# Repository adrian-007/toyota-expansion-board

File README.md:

# Toyota Expansion Board

This is a firmware source code for [Expansion Board](https://adrian-007.eu/2021/02/21/toyota-expansion-board-intro/) I made for my Toyota Corolla after replacing stock radio unit.

Firmware was written in C++14 for ATmega88 MCU and features:

* DS18B20 temperature reading
* SSD1306 OLED display driver
* Six buttons reading via ADC
* Communication with Pioneer radio unit via digital potentiometer MCP42100
* UART output (logging)

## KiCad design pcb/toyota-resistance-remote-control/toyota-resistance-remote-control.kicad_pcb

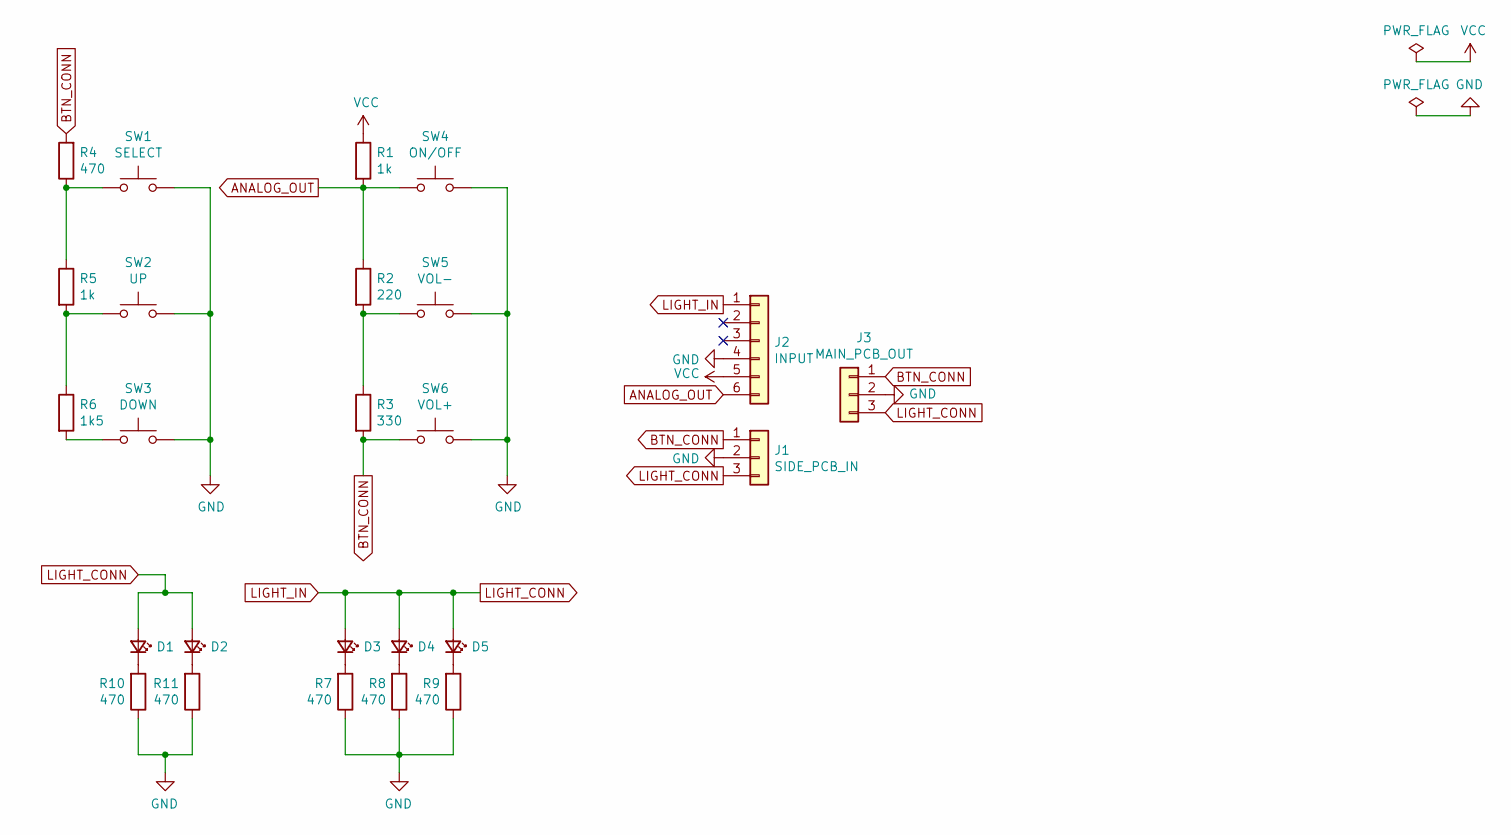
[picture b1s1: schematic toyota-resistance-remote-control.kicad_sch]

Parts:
D1, D2, D3, D4, D5: LED_Small; LED_D3.0mm
J1: SIDE_PCB_IN; PinHeader_1x03_P2.54mm_Vertical
J2: INPUT; PinHeader_1x06_P2.54mm_Vertical
J3: MAIN_PCB_OUT; PinHeader_1x03_P2.54mm_Vertical
R1, R5: 1k; R_1206_3216Metric_Pad1.42x1.75mm_HandSolder
R2: 220; R_1206_3216Metric_Pad1.42x1.75mm_HandSolder
R3: 330; R_1206_3216Metric_Pad1.42x1.75mm_HandSolder
R4, R7, R8, R9, R10, R11: 470; R_1206_3216Metric_Pad1.42x1.75mm_HandSolder
R6: 1k5; R_1206_3216Metric_Pad1.42x1.75mm_HandSolder
SW1: SELECT; SW_PUSH_6mm
SW2: UP; SW_PUSH_6mm
SW3: DOWN; SW_PUSH_6mm
SW4: ON/OFF; SW_PUSH_6mm
SW5: VOL-; SW_PUSH_6mm
SW6: VOL+; SW_PUSH_6mm

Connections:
ANALOG_OUT: J2.6, R1.2, R2.1, SW4.1
BTN_CONN: J1.1, J3.1, R3.2, R4.2, SW6.1
GND: J1.2, J2.4, J3.2, R7.1, R8.1, R9.1, R10.1, R11.1, SW1.2, SW2.2, SW3.2, SW4.2, SW5.2, SW6.2
LIGHT_CONN: D1.2 (A), D2.2 (A), D3.2 (A), D4.2 (A), D5.2 (A), J1.3, J2.1, J3.3
unnamed: D1.1 (K), R10.2
unnamed: D2.1 (K), R11.2
unnamed: D3.1 (K), R7.2
unnamed: D4.1 (K), R8.2
unnamed: D5.1 (K), R9.2
unnamed: R2.2, R3.1, SW5.1
unnamed: R4.1, R5.1, SW1.1
unnamed: R5.2, R6.1, SW2.1
unnamed: R6.2, SW3.1
VCC: J2.5, R1.1

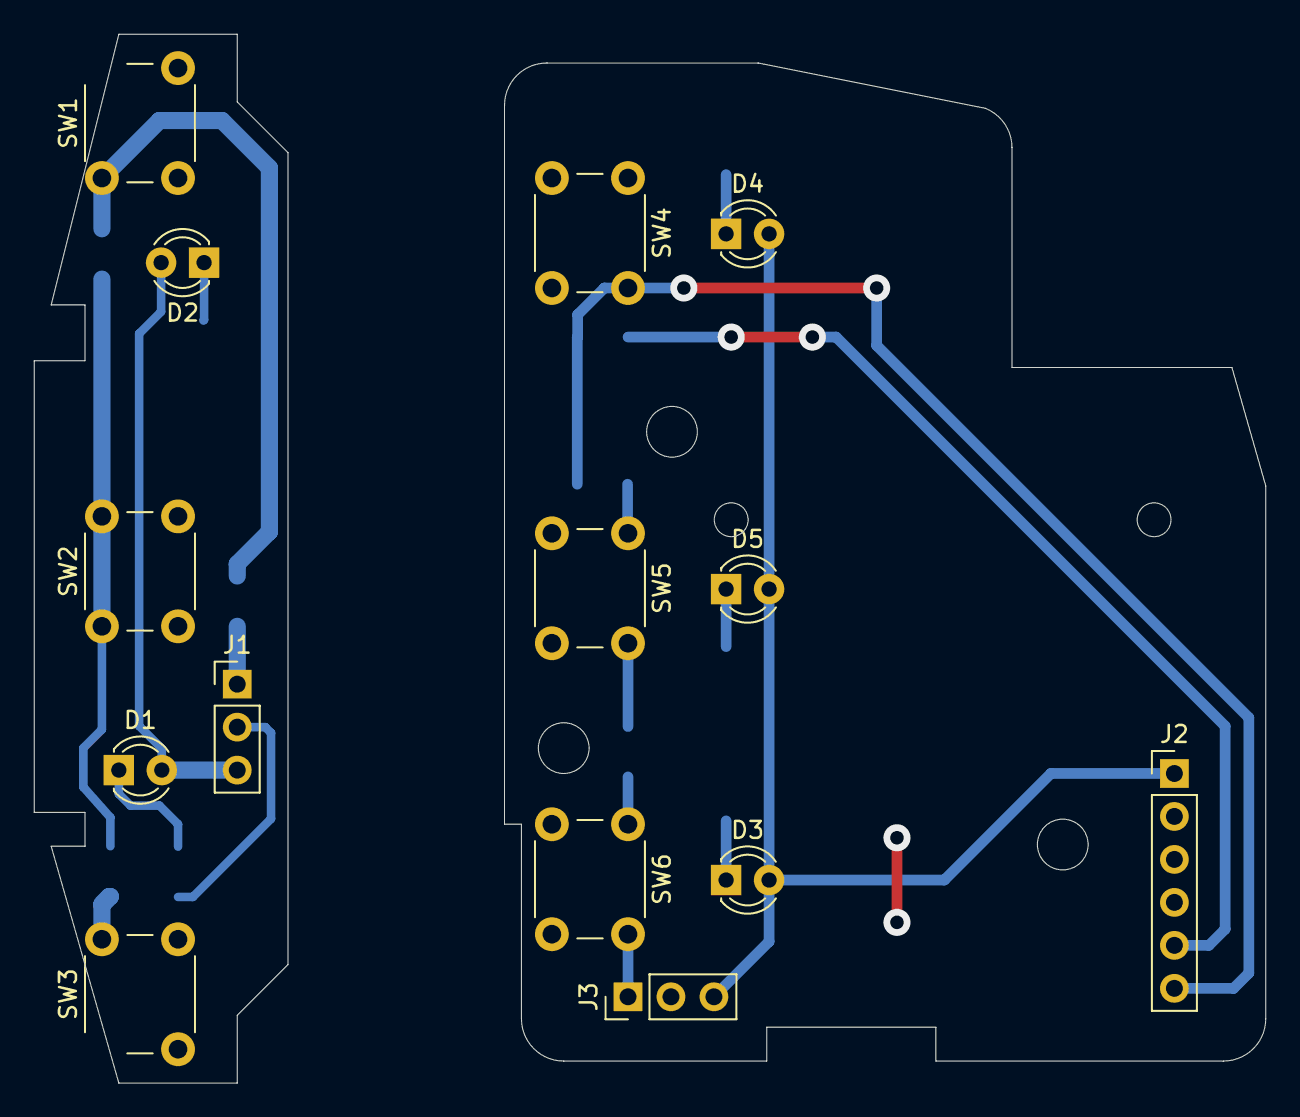
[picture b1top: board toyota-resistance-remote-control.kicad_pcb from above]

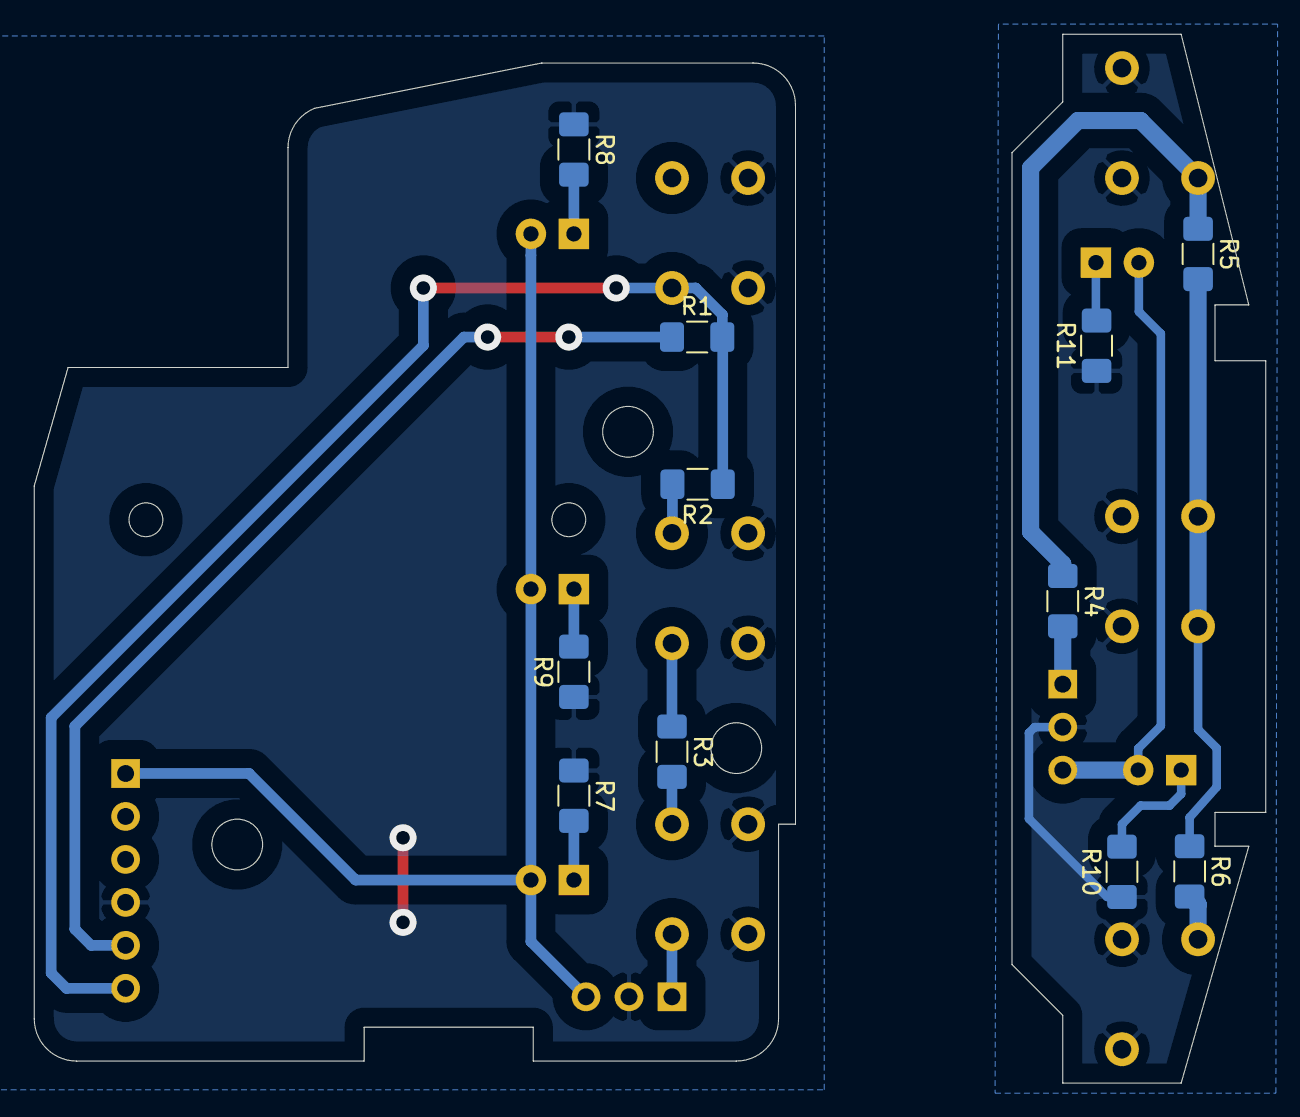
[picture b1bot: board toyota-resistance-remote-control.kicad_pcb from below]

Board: 2 copper layers, 72.8 x 62.0 mm, 25 parts (11 on the bottom side), 14 nets.

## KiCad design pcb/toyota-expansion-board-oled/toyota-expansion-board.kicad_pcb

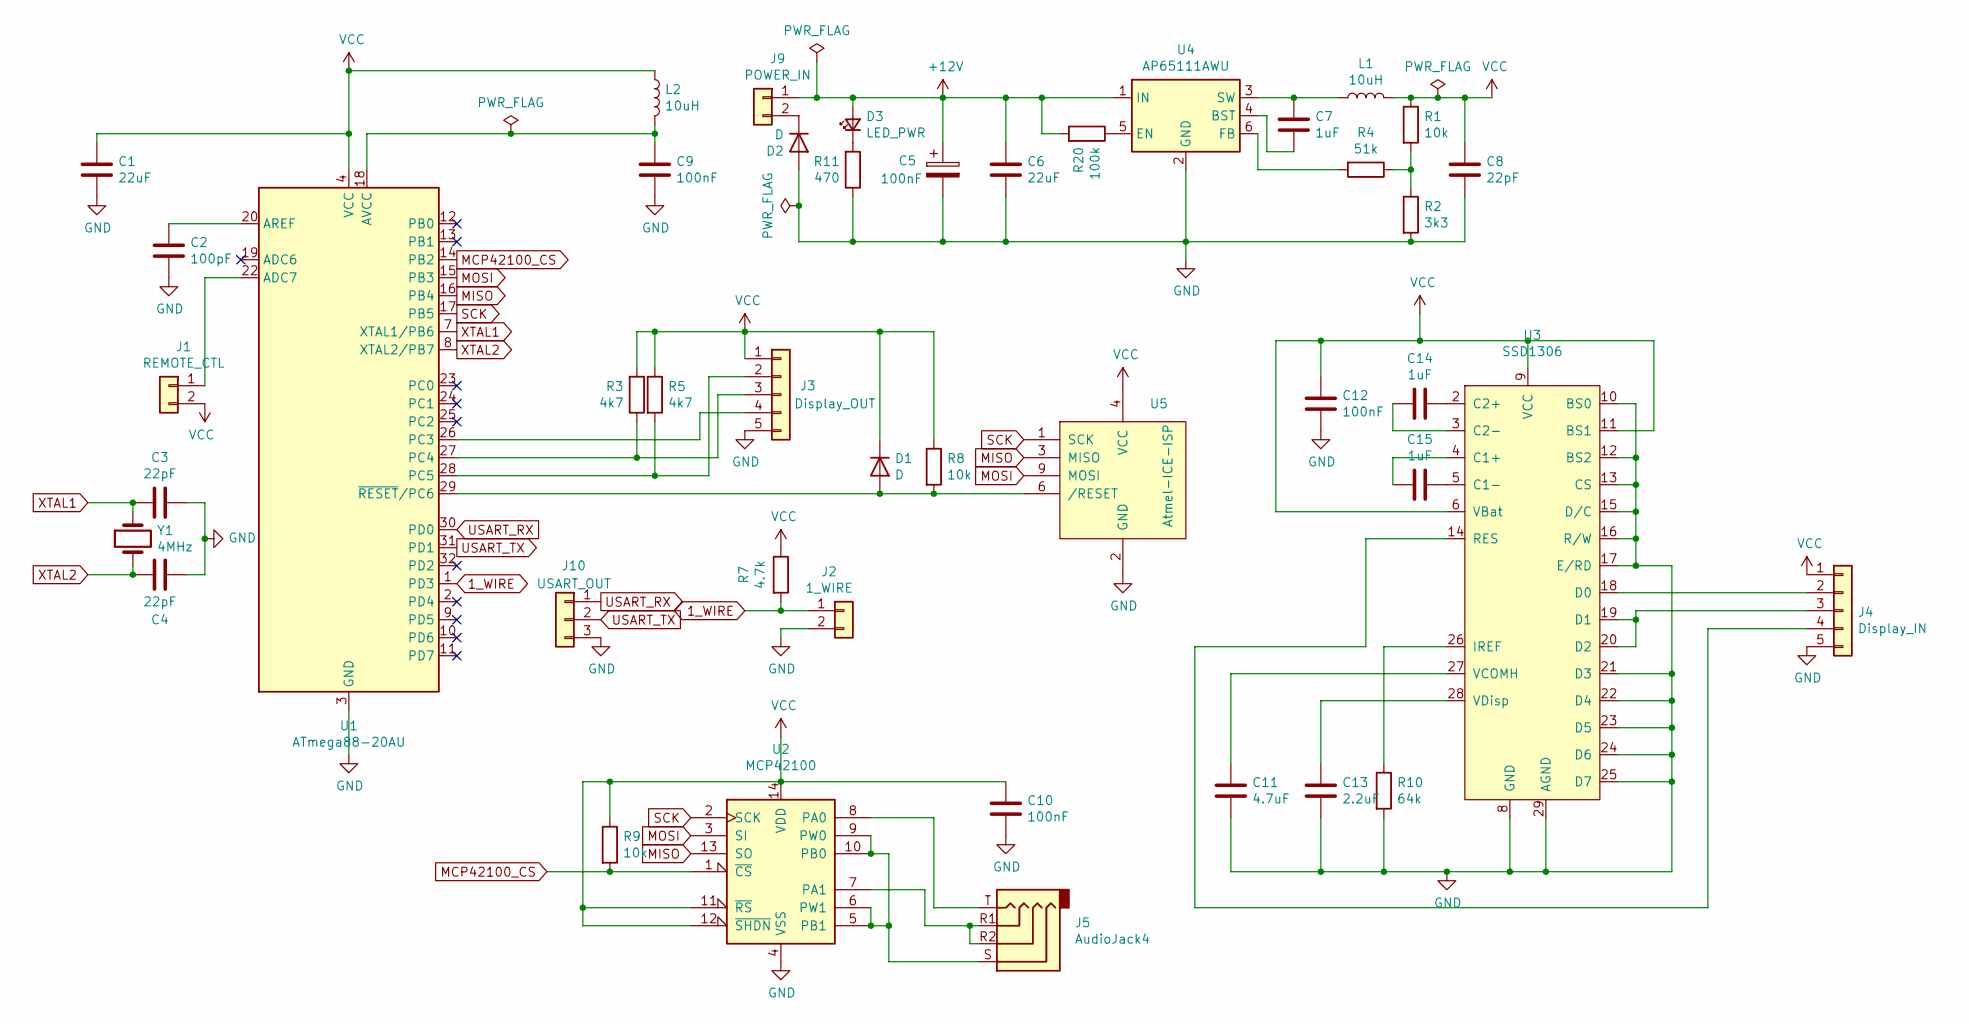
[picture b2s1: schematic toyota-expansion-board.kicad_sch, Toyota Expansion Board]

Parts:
C1, C6: 22uF; CP_Elec_6.3x5.4
C2: 100pF; C_1206_3216Metric_Pad1.33x1.80mm_HandSolder
C3, C4, C8: 22pF; C_1206_3216Metric_Pad1.33x1.80mm_HandSolder
C5, C9, C10, C12: 100nF; C_1206_3216Metric_Pad1.33x1.80mm_HandSolder
C7, C14, C15: 1uF; CP_Elec_4x5.4
C11: 4.7uF; CP_Elec_6.3x5.4
C13: 2.2uF; CP_Elec_6.3x5.4
D1, D2: D; D_DO-15_P5.08mm_Vertical_AnodeUp
D3: LED_PWR; LED_D3.0mm
J1: REMOTE_CTL; TerminalBlock_bornier-2_P5.08mm
J2: 1_WIRE; TerminalBlock_bornier-2_P5.08mm
J3: Display_OUT; PinHeader_1x05_P2.54mm_Vertical
J4: Display_IN; PinHeader_1x05_P2.54mm_Vertical
J5: AudioJack4; PJ218-SMT-LW
J9: POWER_IN; TerminalBlock_bornier-2_P5.08mm
J10: USART_OUT; PinHeader_1x03_P2.54mm_Vertical
L1, L2: 10uH; DLG-0705_HandSolder
R1, R8, R9: 10k; R_1206_3216Metric_Pad1.30x1.75mm_HandSolder
R2: 3k3; R_1206_3216Metric_Pad1.30x1.75mm_HandSolder
R3, R5: 4k7; R_1206_3216Metric_Pad1.30x1.75mm_HandSolder
R4: 51k; R_1206_3216Metric_Pad1.30x1.75mm_HandSolder
R7: 4.7k; R_1206_3216Metric_Pad1.30x1.75mm_HandSolder
R10: 64k; R_1206_3216Metric_Pad1.30x1.75mm_HandSolder
R11: 470; R_1206_3216Metric_Pad1.30x1.75mm_HandSolder
R20: 100k; R_1206_3216Metric_Pad1.30x1.75mm_HandSolder
U1: ATmega88-20AU; TQFP-32_7x7mm_P0.8mm
U2: MCP42100; SOIC-14_3.9x8.7mm_P1.27mm
U3: SSD1306; OLED-AG-L-12864
U4: AP65111AWU; TSOT-23-6
U5: Atmel-ICE-ISP; Atmel-ICE_IDC_2x05_P1.27mm_Vertical
Y1: 4MHz; Crystal_HC18-U_Vertical

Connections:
1_WIRE: J2.1, R7.2, U1.1 (PD3)
+12V: C5.1, C6.1, D3.2 (A), J9.1, R20.2, U4.1 (IN)
GND: C1.2, C2.2, C3.1, C4.2, C5.2, C6.2, C8.2, C9.2, C10.2, C11.2, C12.2, C13.2, D2.2 (A), J2.2, J3.5, J4.5, J10.3, R2.2, R10.2, R11.1, U1.3 (GND), U1.5 (GND), U1.21 (GND), U2.4 (VSS), U3.8 (GND), U3.10 (BS0), U3.12 (BS2), U3.13 (CS), U3.15 (D/C), U3.16 (R/W), U3.17 (E/RD), U3.21 (D3), U3.22 (D4), U3.23 (D5), U3.24 (D6), U3.25 (D7), U3.29 (AGND), U4.2 (GND), U5.2 (GND)
MCP42100_CS: R9.2, U1.14 (PB2), U2.1 (~CS)
MISO: U1.16 (PB4), U2.13 (SO), U5.3 (MISO)
MOSI: U1.15 (PB3), U2.3 (SI), U5.9 (MOSI)
unnamed: C2.1, U1.20 (AREF)
unnamed: C7.1, L1.1, U4.3 (SW)
unnamed: C7.2, U4.4 (BST)
unnamed: C9.1, L2.2, U1.18 (AVCC)
unnamed: C11.1, U3.27 (VCOMH)
unnamed: C13.1, U3.28 (VDisp)
unnamed: C14.1, U3.3 (C2-)
unnamed: C14.2, U3.2 (C2+)
unnamed: C15.1, U3.5 (C1-)
unnamed: C15.2, U3.4 (C1+)
unnamed: D1.2 (A), R8.2, U1.29 (~RESET/PC6), U5.6 (/RESET)
unnamed: D2.1 (K), J9.2
unnamed: D3.1 (K), R11.2
unnamed: J1.1, U1.22 (ADC7)
unnamed: J3.2, R5.2, U1.28 (PC5)
unnamed: J3.3, R3.1, U1.27 (PC4)
unnamed: J3.4, U1.26 (PC3)
unnamed: J4.2, U3.18 (D0)
unnamed: J4.3, U3.19 (D1), U3.20 (D2)
unnamed: J4.4, U3.14 (RES)
unnamed: J5.R1, J5.R2, U2.7 (PA1)
unnamed: J5.S, U2.5 (PB1), U2.6 (PW1), U2.9 (PW0), U2.10 (PB0)
unnamed: J5.T, U2.8 (PA0)
unnamed: R1.2, R2.1, R4.1
unnamed: R4.2, U4.6 (FB)
unnamed: R10.1, U3.26 (IREF)
unnamed: R20.1, U4.5 (EN)
SCK: U1.17 (PB5), U2.2 (SCK), U5.1 (SCK)
USART_RX: J10.1, U1.30 (PD0)
USART_TX: J10.2, U1.31 (PD1)
VCC: C1.1, C8.1, C10.1, C12.1, D1.1 (K), J1.2, J3.1, J4.1, L1.2, L2.1, R1.1, R3.2, R5.1, R7.1, R8.1, R9.1, U1.4 (VCC), U1.6 (VCC), U2.11 (~RS), U2.12 (~SHDN), U2.14 (VDD), U3.6 (VBat), U3.9 (VCC), U3.11 (BS1), U5.4 (VCC)
XTAL1: C3.2, U1.7 (XTAL1/PB6), Y1.1
XTAL2: C4.1, U1.8 (XTAL2/PB7), Y1.2

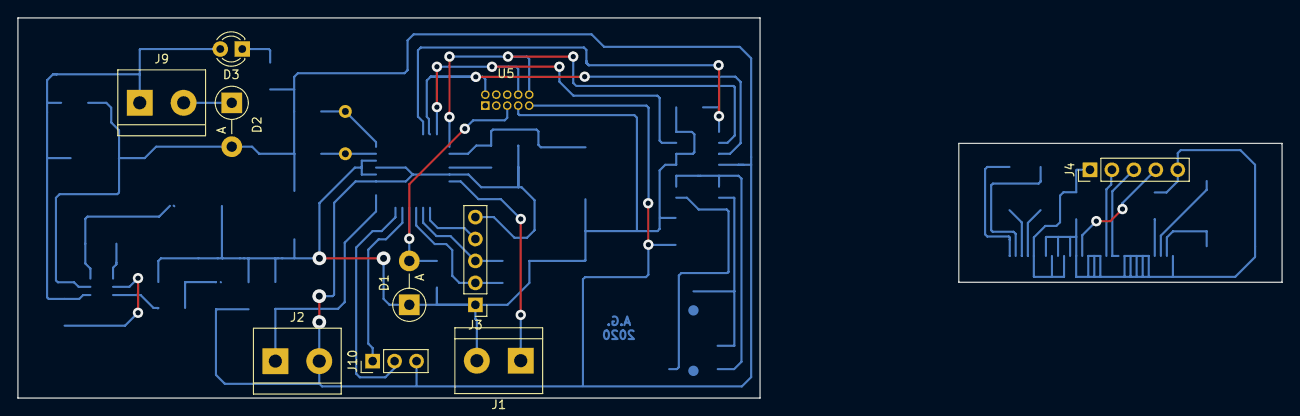
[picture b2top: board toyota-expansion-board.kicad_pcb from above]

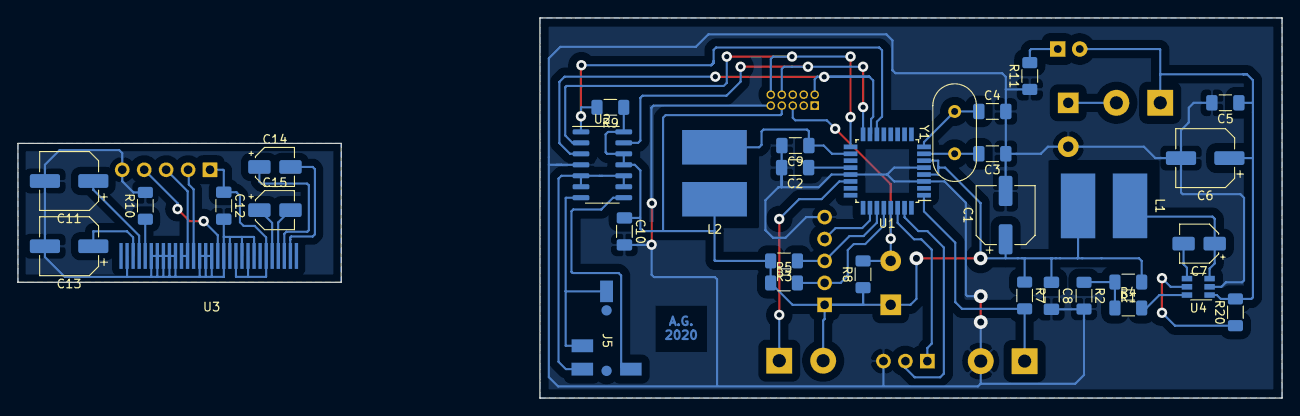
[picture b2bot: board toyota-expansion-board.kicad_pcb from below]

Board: 2 copper layers, 146.3 x 44.0 mm, 44 parts (34 on the bottom side), 39 nets.

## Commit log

2021-03-06 Initial production version
2021-03-06 Add README.md
2021-03-06 Convert tabs to spaces
2023-07-08 Add KiCAD project files
